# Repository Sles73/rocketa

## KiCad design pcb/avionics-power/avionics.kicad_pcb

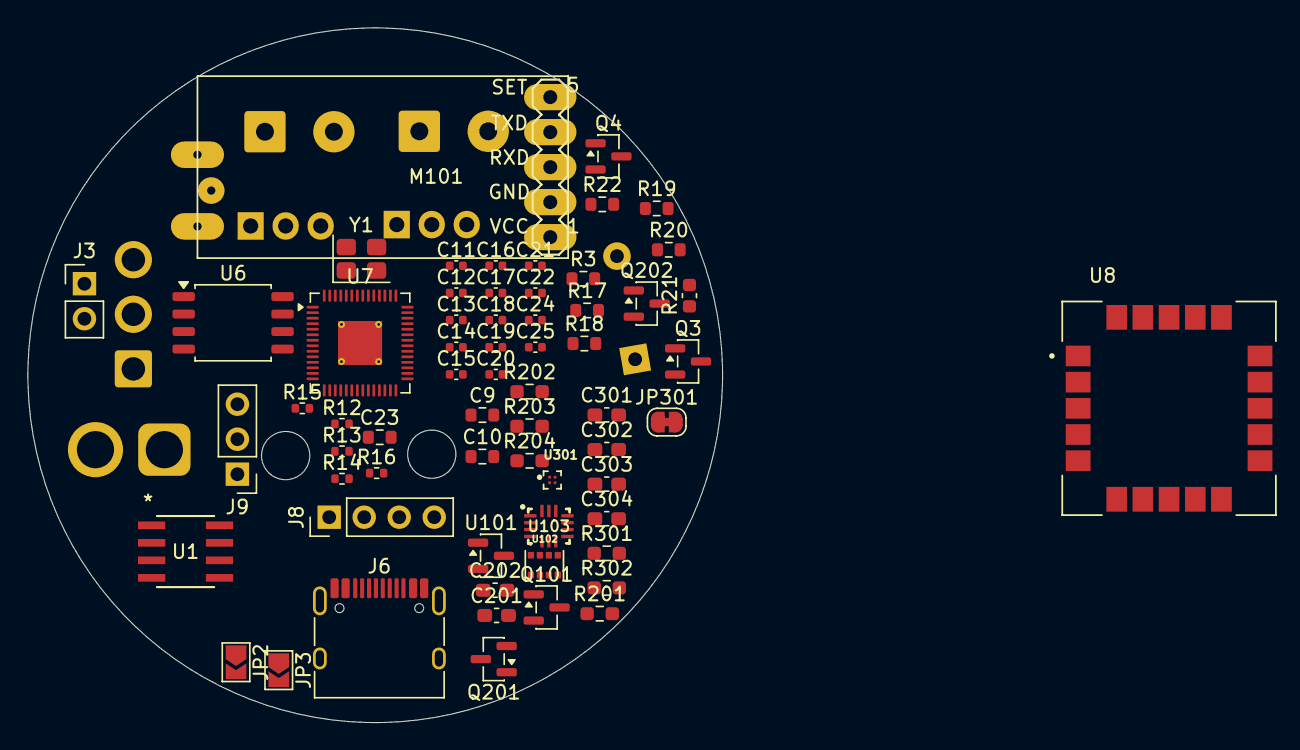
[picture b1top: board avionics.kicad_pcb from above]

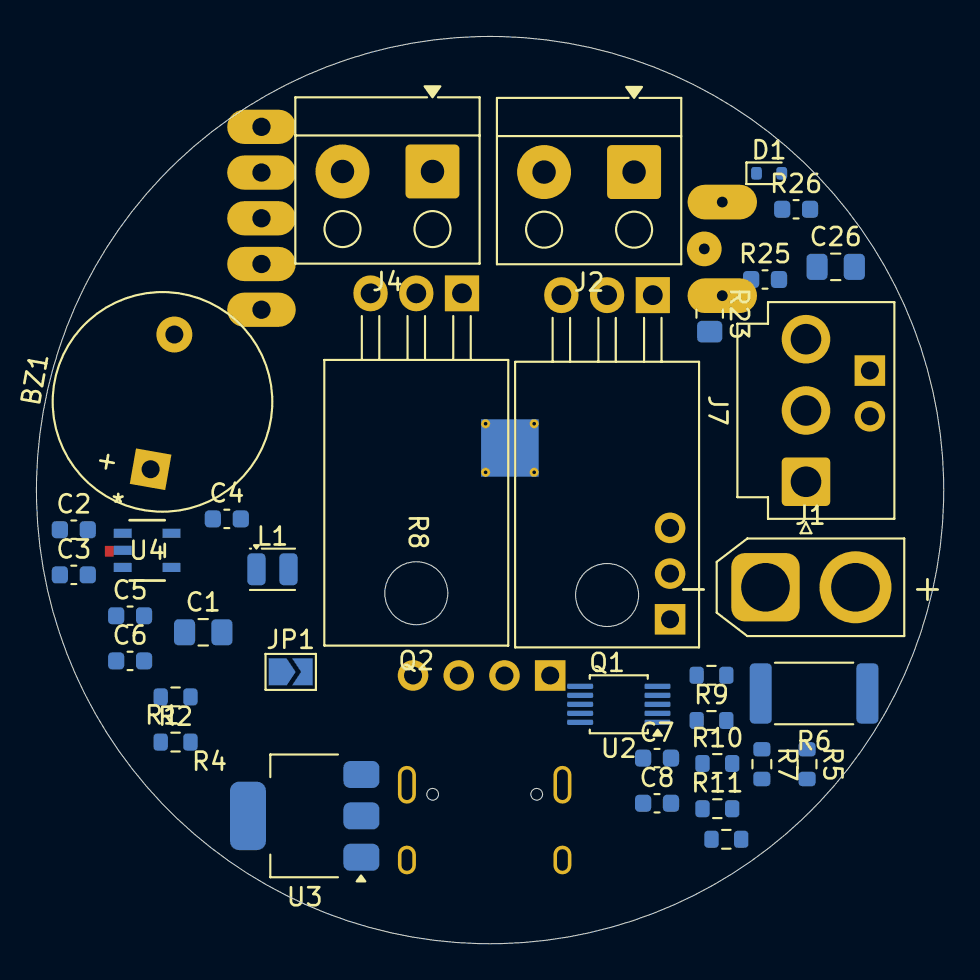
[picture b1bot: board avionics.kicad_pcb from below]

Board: 2 copper layers, 50.4 x 50.4 mm, 102 parts (35 on the bottom side), 55 nets, no tracks yet.

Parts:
BZ1: Buzzer; Buzzer_12x9.5RM7.6
C1: 22uF; C_0805_2012Metric_Pad1.18x1.45mm_HandSolder
C2: 10uF; C_0603_1608Metric
C3, C5, C6: 22uF; C_0603_1608Metric
C4: 22pF; C_0603_1608Metric
C7, C8: 100nF; C_0603_1608Metric
C9, C10, C23: 10u; R_0603_1608Metric
C11, C12, C13, C14, C15, C16, C17, C18, C19, C22: 100n; C_0402_1005Metric
C20, C21: 1u; C_0402_1005Metric
C24, C25: 15p; C_0402_1005Metric
C26: 1uF; C_0805_2012Metric_Pad1.18x1.45mm_HandSolder
C201, C202: 1uF; C_0603_1608Metric_Pad1.08x0.95mm_HandSolder
C301, C302, C303: 100nF; C_0603_1608Metric_Pad1.08x0.95mm_HandSolder
C304: 2.2uF; C_0603_1608Metric_Pad1.08x0.95mm_HandSolder
D1: ESD5Z3V3; D_SOD-523
H1, H2, H3, H4: MountingHole; MountingHole_2.7mm_M2.5
J1: Conn_batt; AMASS_XT30U-F_1x02_P5.0mm_Vertical
J2, J4: Palník_Terminal_01x02; Altech_AK100_1x02_P5.00mm
J3: Conn_01x02; PinHeader_1x02_P2.54mm_Vertical
J6: USB_C_Receptacle_USB2.0_16P; USB_C_Receptacle_HRO_TYPE-C-31-M-12
J7: RFB_switch; JST_VH_B3P-VH-B_1x03_P3.96mm_Vertical
J8: Conn_01x04_Pin; PinHeader_1x04_P2.54mm_Vertical
J9: Conn_01x03_Pin; PinHeader_1x03_P2.54mm_Vertical
JP1: SolderJumper_2_Open; SolderJumper-2_P1.3mm_Open_TrianglePad1.0x1.5mm
JP2: A1; SolderJumper-2_P1.3mm_Open_TrianglePad1.0x1.5mm
JP3: A0; SolderJumper-2_P1.3mm_Open_TrianglePad1.0x1.5mm
JP301: i2c; SolderJumper-2_P1.3mm_Bridged_RoundedPad1.0x1.5mm
L1: 2.2uH; L_Coilcraft_0805HQ_2012Metric
M101: HC-12; MA05-1
Q1, Q2: IRF9540N; TO-220-3_Horizontal_TabDown
Q3, Q4, Q202: SS8050; SOT-23
Q101, Q201: 2N7002; SOT-23
R1, R3, R7, R8, R9, R10, R11, R18, R19: 10k; R_0603_1608Metric
R2: 45k; R_0603_1608Metric
R4, R5: 10R; R_0603_1608Metric
R6: 5m; R_2512_6332Metric
R12, R13: 27; R_0402_1005Metric
R14: DNF; R_0402_1005Metric
R15, R16: 1k; R_0402_1005Metric
R17, R20, R22: 1k; R_0603_1608Metric
R21: 1k; C_0603_1608Metric
R23: 470R; R_0805_2012Metric_Pad1.20x1.40mm_HandSolder
R25: 10K; C_0603_1608Metric
R26: 18k; C_0603_1608Metric
R201, R202, R203, R204: 10k; R_0603_1608Metric_Pad0.98x0.95mm_HandSolder
R301, R302: 2.7k; R_0603_1608Metric_Pad0.98x0.95mm_HandSolder
U1: ATTINY402-SSNR; SOIC8_4P9X3P9MC_MCH
U2: INA226; TSSOP-10_3x3mm_P0.5mm
U3: AMS1117-3.3; SOT-223-3_TabPin2
U4: SY8089AAAC; SY8089AAAC_SGY
U6: W25Q128JVS; SOIC-8_5.3x5.3mm_P1.27mm
U7: RP2040; QFN-56-1EP_7x7mm_P0.4mm_EP3.2x3.2mm_ThermalVias
U8: SAM-M8Q-0-10; MODULE_SAM-M8Q-0-10
U101: ME6206A18XG; SOT-23
U102: ICP-10111; PSON65P250X200X100-8N
U103: LSM6DS3TR-C; LGA-14-2.5X3MM
U301: MMC5603NJ; XDCR_MMC5603NJ
Y1: ABM8-272-T3; Crystal_SMD_3225-4Pin_3.2x2.5mm

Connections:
+1V1: C11.1, C12.1, C20.1, U7.23 (DVDD), U7.45 (VREG_VOUT), U7.50 (DVDD)
+3V3: C4.1, C5.1, C6.1, C8.2, C10.1, C13.1, C14.1, C15.1, C16.1, C17.1, C18.1, C19.1, C21.1, C22.1, C23.1, C201.1, C301.1, C302.1, C303.1, C304.1, J8.2, J9.2, JP1.2 (B), JP2.2 (B), JP3.2 (B), JP301.1 (A), L1.2, R2.1, R9.2, R10.2, R11.2, R14.1, R202.1, R204.1, R301.1, R302.1, U1.1 (VDD), U2.6 (VS), U6.8 (VCC), U7.1 (IOVDD), U7.10 (IOVDD), U7.22 (IOVDD), U7.33 (IOVDD), U7.42 (IOVDD), U7.43 (ADC_AVDD), U7.44 (VREG_IN), U7.48 (USB_VDD), U7.49 (IOVDD), U101.3 (VI), U103.5 (VDDIO), U103.8 (VDD), U301.B1 (VDD)
+VDC: BZ1.1 (+), C1.1, C2.2, J7.1, R1.1, R5.2, R6.2, R26.1, U3.3 (VI), U4.4 (IN)
/GPS/+3V3: U8.2 (VCC_IO), U8.3 (V_BCKP), U8.17 (VCC)
/IMU/SCL: R302.2, U103.13 (SCL), U301.A2 (SCL)
/IMU/SDA: R301.2, U103.14 (SDA), U301.B2 (SDA)
/backup_mtp/palnik_backup: R20.2, U1.4 (PA1)
/barometr/SCL: Q101.3 (D), R202.2
/barometr/SDA: Q201.3 (D), R204.2
/ejection_charge_safety/Sw1: C26.1, R23.1
/ejection_charge_safety/VCC_palnik: J7.3, Q1.3 (S), Q2.3 (S), R18.2, R19.2
/mcu/QSPI_SCLK: U6.6 (CLK), U7.52 (QSPI_SCLK)
/mcu/QSPI_SD0: U6.5 (DI(IO0)), U7.53 (QSPI_SD0)
/mcu/QSPI_SD1: U6.2 (DO(IO1)), U7.55 (QSPI_SD1)
/mcu/QSPI_SD2: U6.3 (IO2), U7.54 (QSPI_SD2)
/mcu/QSPI_SD3: U6.7 (IO3), U7.51 (QSPI_SD3)
/mcu/QSPI_SS: R14.2, R15.1, U6.1 (~CS), U7.56 (QSPI_SS)
/mcu/USB_D+: J6.A6 (D+), J6.B6 (D+), R12.1
/mcu/USB_D-: J6.A7 (D-), J6.B7 (D-), R13.1
/mcu/XIN: C24.1, U7.20 (XIN), Y1.1
/mcu/XOUT: R16.1, U7.21 (XOUT)
/mcu/~USB_BOOT: J3.1, R15.2
/power_management/Alert: R11.1, U2.3 (~Alert)
/power_management/SCL: R10.1, U2.5 (SCL)
/power_management/SDA: R9.1, U2.4 (SDA)
/power_management/VCC_batt: J1.2, R4.2, R6.1, U2.8 (Vbus)
GND: C1.2, C2.1, C3.1, C5.2, C6.2, C9.2, C10.2, C11.2, C12.2, C13.2, C14.2, C15.2, C16.2, C17.2, C18.2, C19.2, C20.2, C21.2, C22.2, C23.2, C24.2, C25.2, C26.2, C201.2, C202.2, C301.2, C302.2, C303.2, C304.2, D1.2 (A), J1.1, J2.1, J3.2, J4.1, J6.A1 (GND), J6.A12 (GND), J6.B1 (GND), J6.B12 (GND), J6.SH (SHIELD), J8.1, J9.3, Q3.2 (E), Q4.2 (E), Q202.2 (E), R3.2, R7.1, R8.1, R25.2, U1.8 (GND), U2.7 (GND), U3.1 (GND), U4.2 (GND), U6.4 (GND), U7.19 (TESTEN), U7.57 (GND), U8.1 (GND), U8.4 (GND), U8.5 (GND), U8.6 (GND), U8.10 (GND), U8.11 (GND), U8.15 (GND), U8.16 (GND), U8.20 (GND), U101.1 (GND), U102.1 (GND), U102.5 (RESV5), U102.7 (GND), U103.1 (SDO/SA0), U103.2 (SDX), U103.3 (SCX), U103.6 (GND), U103.7 (GND), U301.A1 (VSA), Y1.2, Y1.4
unnamed: BZ1.2 (-), Q4.3 (C)
unnamed: C25.1, R16.2, Y1.3
unnamed: D1.1 (K), J7.2, R23.2, R25.1, R26.2
unnamed: J2.2, Q1.2 (D)
unnamed: J4.2, Q2.2 (D)
unnamed: J8.3, J9.1, R21.2, U1.6 (PA0/RESET/UPDI)
unnamed: J8.4, R21.1
unnamed: C3.2, JP1.1 (A), U3.2 (VO)
unnamed: JP2.1 (A), R7.2, U2.1 (A1)
unnamed: JP3.1 (A), R8.2, U2.2 (A0)
unnamed: JP301.2 (B), U103.12 (CS)
unnamed: M101.GND (GND1), M101.GND1
unnamed: Q1.1 (G), Q3.3 (C), R19.1
unnamed: Q2.1 (G), Q202.3 (C), R18.1
unnamed: Q3.1 (B), R20.1
unnamed: Q4.1 (B), R22.1
unnamed: C202.1, Q101.1 (G), Q201.1 (G), R201.1, R203.1, U101.2 (VO), U102.8 (VDD)
unnamed: Q101.2 (S), R201.2, U102.4 (SCL)
unnamed: Q201.2 (S), R203.2, U102.3 (SDA)
unnamed: Q202.1 (B), R17.1
unnamed: C7.1, R4.1, U2.10 (Vin+)
unnamed: C7.2, R5.1, U2.9 (Vin-)
unnamed: R1.2, U4.1 (EN)
unnamed: C4.2, R2.2, R3.1, U4.5 (FB)
unnamed: L1.1, U4.3 (LX)
unnamed: R13.2, U7.46 (USB_DM)
unnamed: R12.2, U7.47 (USB_DP)
VBUS: C9.1, J6.A4 (VBUS), J6.A9 (VBUS), J6.B4 (VBUS), J6.B9 (VBUS)

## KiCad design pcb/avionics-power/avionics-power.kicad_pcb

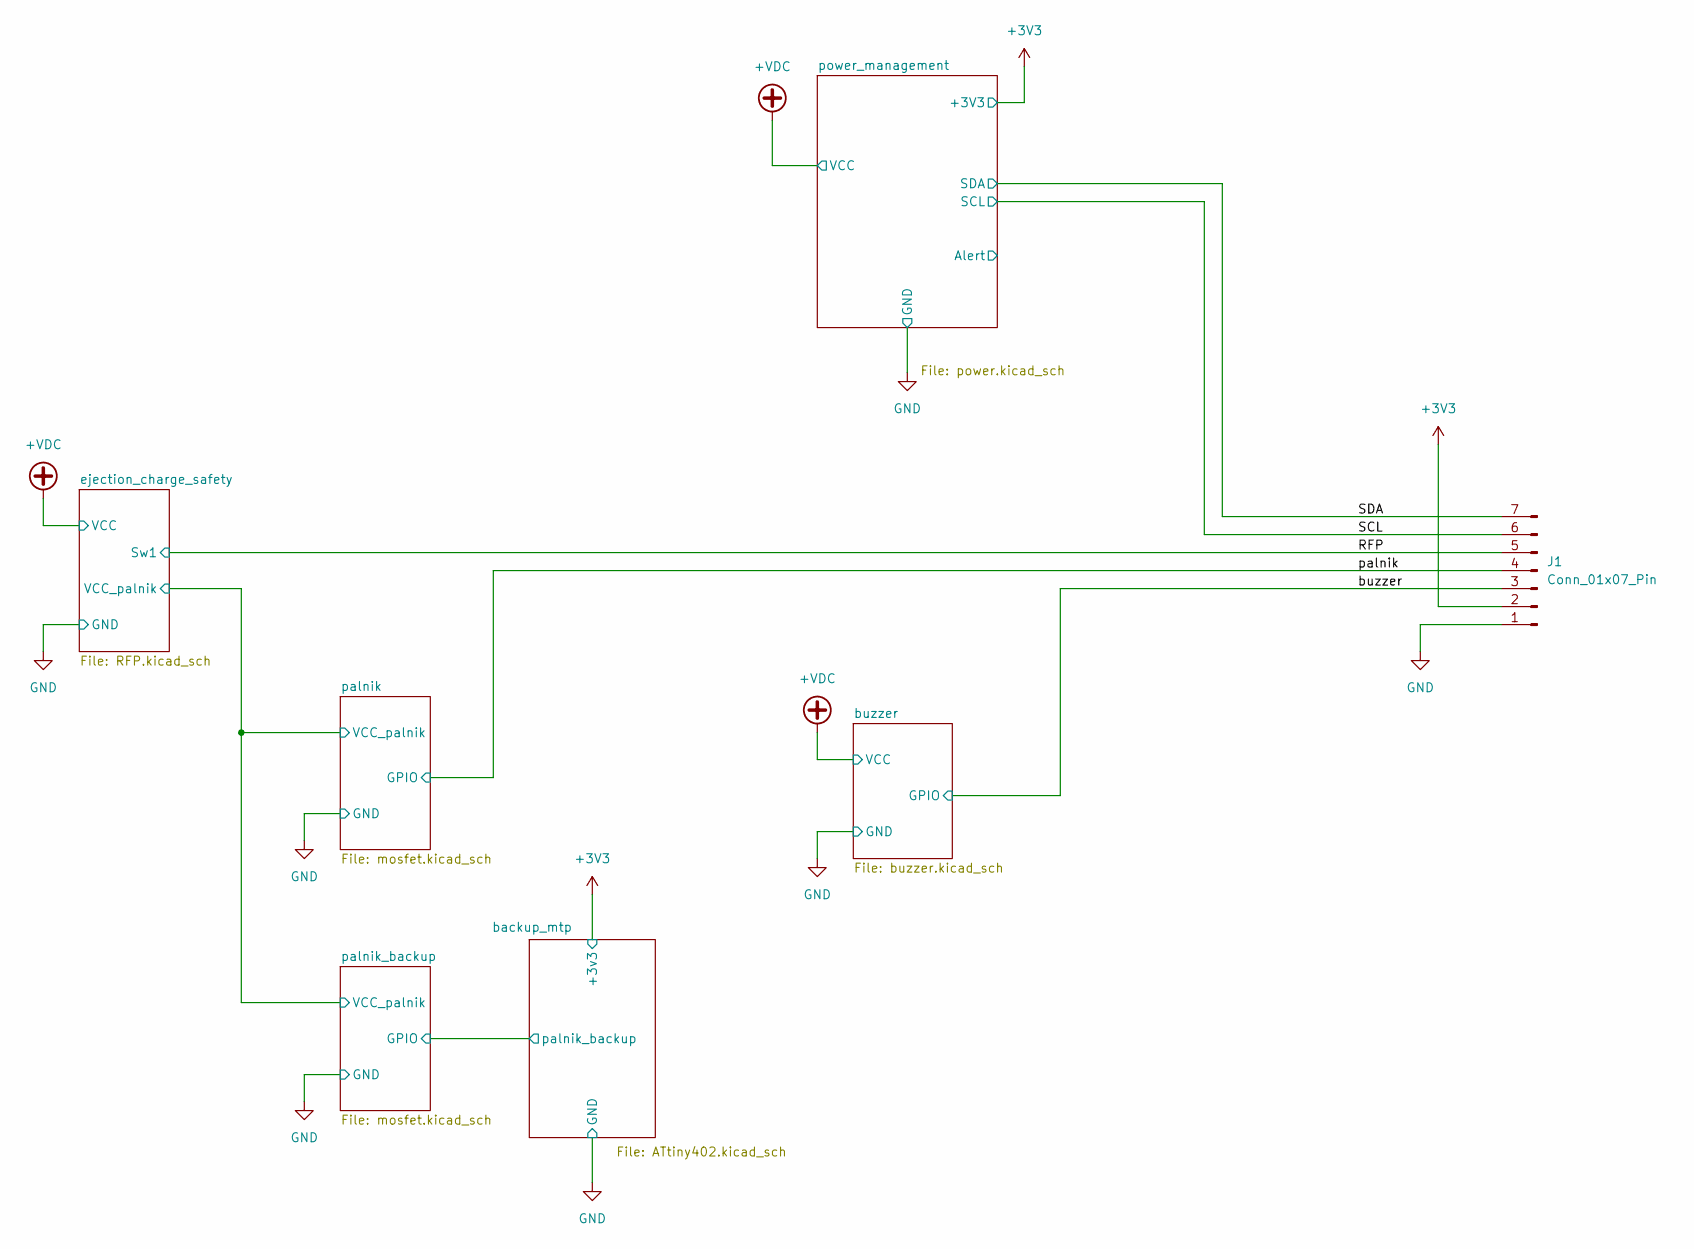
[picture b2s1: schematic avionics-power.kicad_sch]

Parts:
J1: Conn_01x07_Pin; JST_XA_S07B-XASK-1_1x07_P2.50mm_Horizontal

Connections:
+3V3: J1.2; also elsewhere on the board
/buzzer/GPIO: J1.3; also elsewhere on the board
/ejection_charge_safety/Sw1: J1.5; also elsewhere on the board
/palnik/GPIO: J1.4; also elsewhere on the board
/power_management/SCL: J1.6; also elsewhere on the board
/power_management/SDA: J1.7; also elsewhere on the board
GND: J1.1; also elsewhere on the board

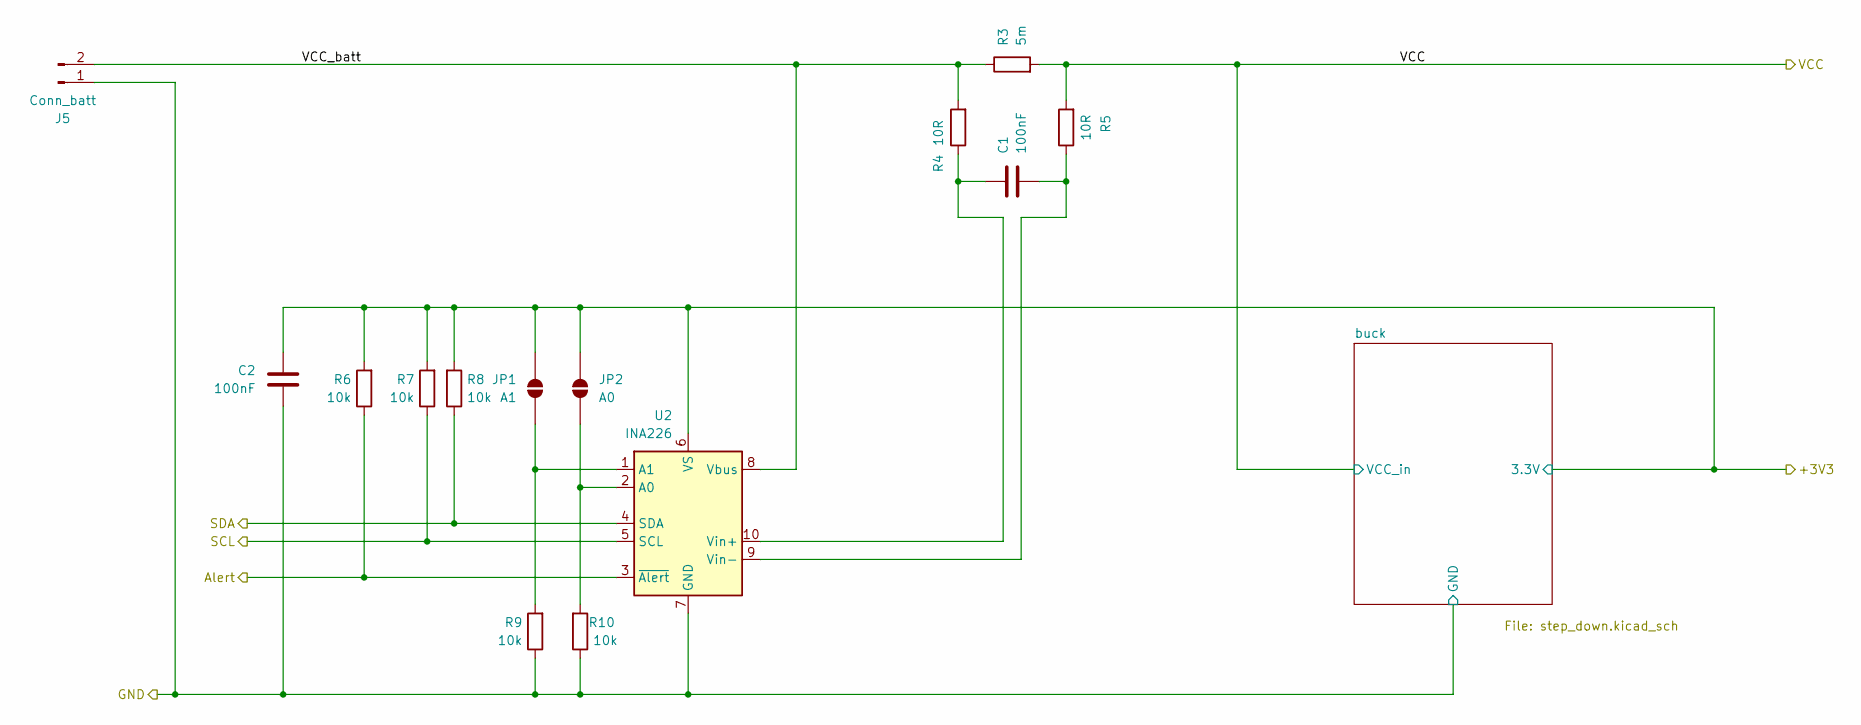
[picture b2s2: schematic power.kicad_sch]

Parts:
C1, C2: 100nF; C_0603_1608Metric
J5: Conn_batt; AMASS_XT30U-F_1x02_P5.0mm_Vertical
JP1: A1; SolderJumper-2_P1.3mm_Open_TrianglePad1.0x1.5mm
JP2: A0; SolderJumper-2_P1.3mm_Open_TrianglePad1.0x1.5mm
R3: 5m; R_2512_6332Metric
R4, R5: 10R; R_0603_1608Metric
R6, R7, R8, R9, R10: 10k; R_0603_1608Metric
U2: INA226; TSSOP-10_3x3mm_P0.5mm

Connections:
+3V3: C2.2, JP1.2 (B), JP2.2 (B), R6.2, R7.2, R8.2, U2.6 (VS); also elsewhere on the board
+VDC: R3.2, R5.2; also elsewhere on the board
/power_management/Alert: R6.1, U2.3 (~Alert)
/power_management/SCL: R7.1, U2.5 (SCL); also elsewhere on the board
/power_management/SDA: R8.1, U2.4 (SDA); also elsewhere on the board
/power_management/VCC_batt: J5.2, R3.1, R4.2, U2.8 (Vbus)
GND: C2.1, J5.1, R9.1, R10.1, U2.7 (GND); also elsewhere on the board
unnamed: JP1.1 (A), R9.2, U2.1 (A1)
unnamed: JP2.1 (A), R10.2, U2.2 (A0)
unnamed: C1.1, R4.1, U2.10 (Vin+)
unnamed: C1.2, R5.1, U2.9 (Vin-)

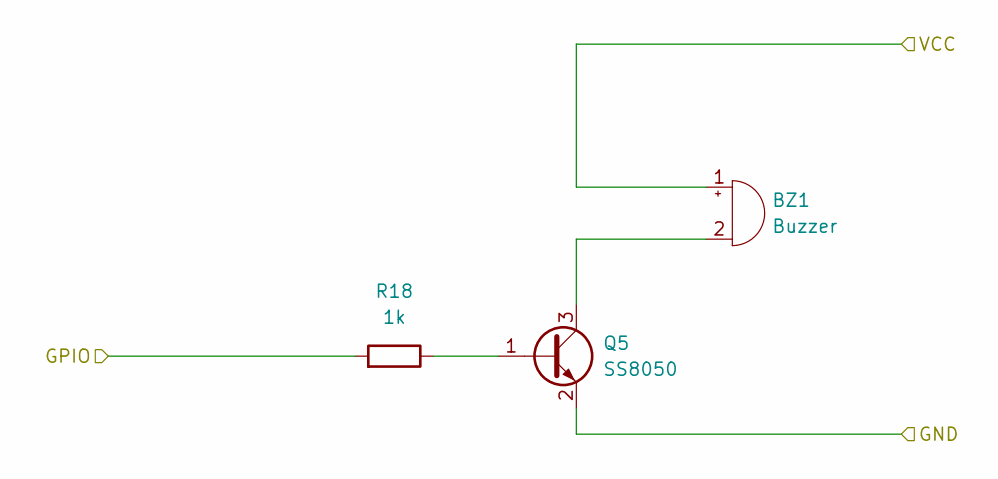
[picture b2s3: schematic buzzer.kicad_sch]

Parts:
BZ1: Buzzer; Buzzer_12x9.5RM7.6
Q5: SS8050; SOT-23
R18: 1k; R_0603_1608Metric

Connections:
+VDC: BZ1.1 (+); also elsewhere on the board
/buzzer/GPIO: R18.2; also elsewhere on the board
GND: Q5.2 (E); also elsewhere on the board
unnamed: BZ1.2 (-), Q5.3 (C)
unnamed: Q5.1 (B), R18.1

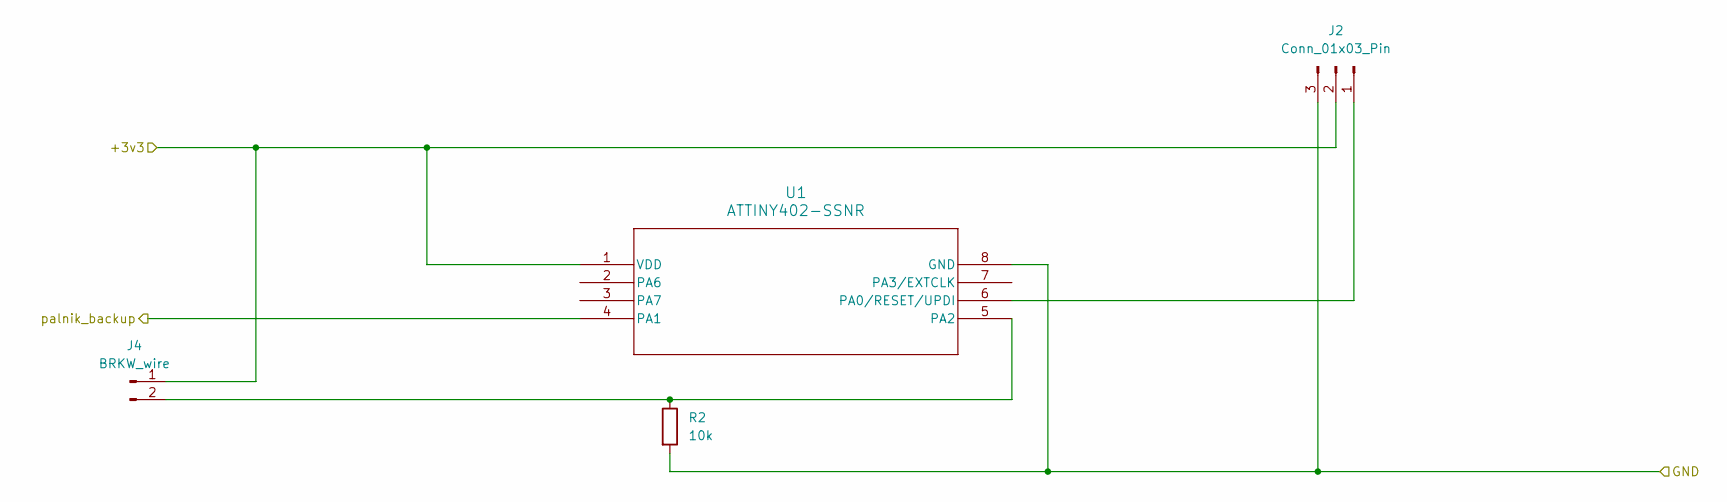
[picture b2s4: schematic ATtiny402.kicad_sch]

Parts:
J2: Conn_01x03_Pin; PinHeader_1x03_P2.54mm_Vertical
J4: BRKW_wire; JST_PH_B2B-PH-K_1x02_P2.00mm_Vertical
R2: 10k; C_0603_1608Metric
U1: ATTINY402-SSNR; SOIC8_4P9X3P9MC_MCH

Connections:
+3V3: J2.2, J4.1, U1.1 (VDD); also elsewhere on the board
/backup_mtp/palnik_backup: U1.4 (PA1); also elsewhere on the board
GND: J2.3, R2.2, U1.8 (GND); also elsewhere on the board
unnamed: J2.1, U1.6 (PA0/RESET/UPDI)
unnamed: J4.2, R2.1, U1.5 (PA2)

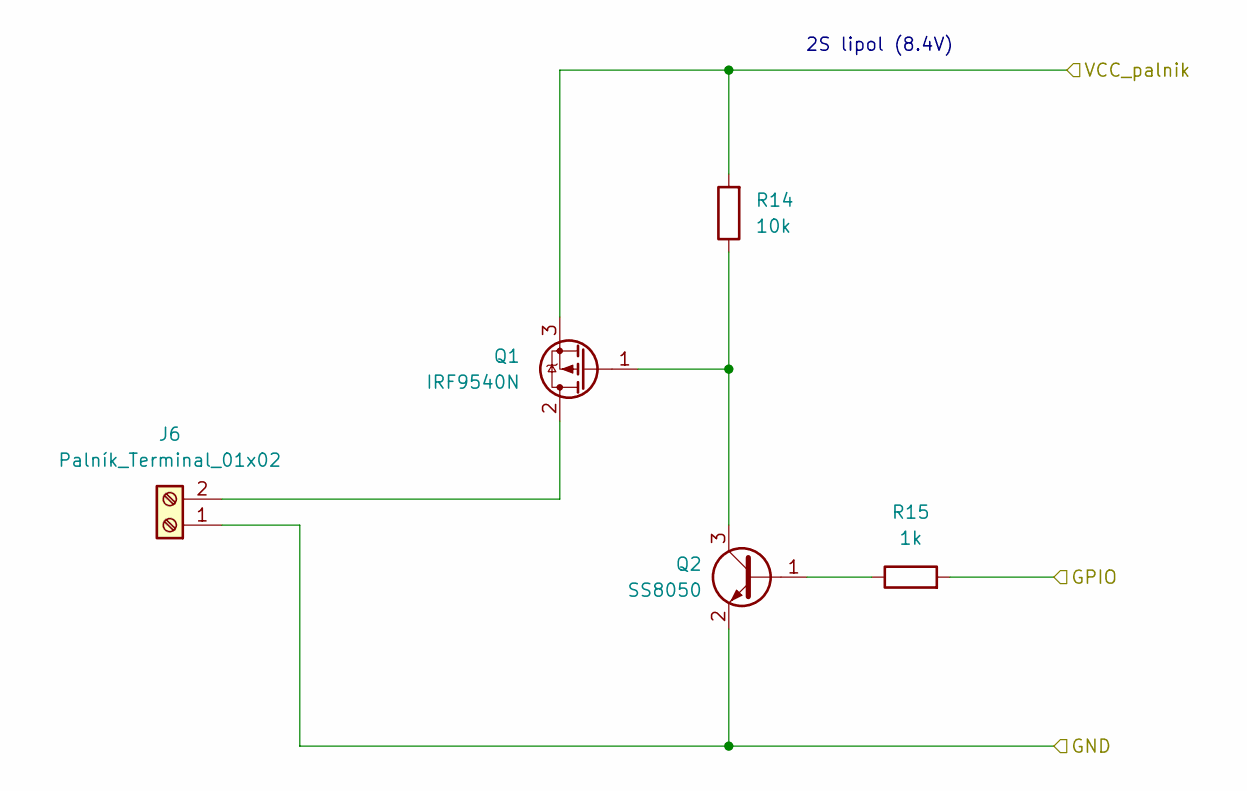
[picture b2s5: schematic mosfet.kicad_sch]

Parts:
J6: Palník_Terminal_01x02; Altech_AK100_1x02_P5.00mm
Q1: IRF9540N; TO-220-3_Horizontal_TabDown
Q2: SS8050; SOT-23
R14: 10k; R_0603_1608Metric
R15: 1k; R_0603_1608Metric

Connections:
/ejection_charge_safety/VCC_palnik: Q1.3 (S), R14.2; also elsewhere on the board
/palnik/GPIO: R15.2; also elsewhere on the board
GND: J6.1, Q2.2 (E); also elsewhere on the board
unnamed: J6.2, Q1.2 (D)
unnamed: Q1.1 (G), Q2.3 (C), R14.1
unnamed: Q2.1 (B), R15.1

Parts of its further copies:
J7: Palník_Terminal_01x02; Altech_AK100_1x02_P5.00mm
Q3: IRF9540N; TO-220-3_Horizontal_TabDown
Q4: SS8050; SOT-23
R16: 10k; R_0603_1608Metric
R17: 1k; R_0603_1608Metric

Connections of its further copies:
/backup_mtp/palnik_backup: R17.2; also elsewhere on the board
/ejection_charge_safety/VCC_palnik: Q3.3 (S), R16.2; also elsewhere on the board
GND: J7.1, Q4.2 (E); also elsewhere on the board
unnamed: J7.2, Q3.2 (D)
unnamed: Q3.1 (G), Q4.3 (C), R16.1
unnamed: Q4.1 (B), R17.1

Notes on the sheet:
2S lipol (8.4V)

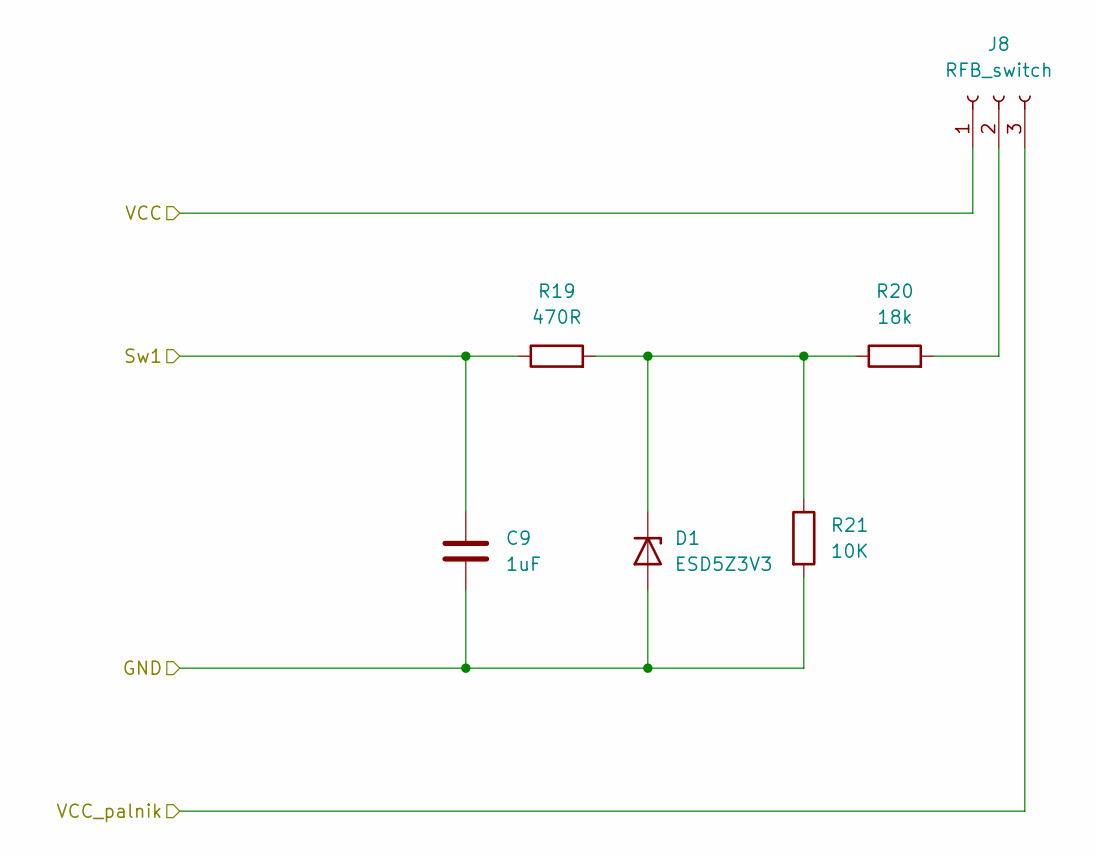
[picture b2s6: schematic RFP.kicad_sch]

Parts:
C9: 1uF; C_0805_2012Metric_Pad1.18x1.45mm_HandSolder
D1: ESD5Z3V3; D_SOD-523
J8: RFB_switch; JST_VH_B3P-VH-B_1x03_P3.96mm_Vertical
R19: 470R; R_0805_2012Metric_Pad1.20x1.40mm_HandSolder
R20: 18k; C_0603_1608Metric
R21: 10K; C_0603_1608Metric

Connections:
+VDC: J8.1; also elsewhere on the board
/ejection_charge_safety/Sw1: C9.1, R19.1; also elsewhere on the board
/ejection_charge_safety/VCC_palnik: J8.3; also elsewhere on the board
GND: C9.2, D1.2 (A), R21.2; also elsewhere on the board
unnamed: D1.1 (K), R19.2, R20.1, R21.1
unnamed: J8.2, R20.2

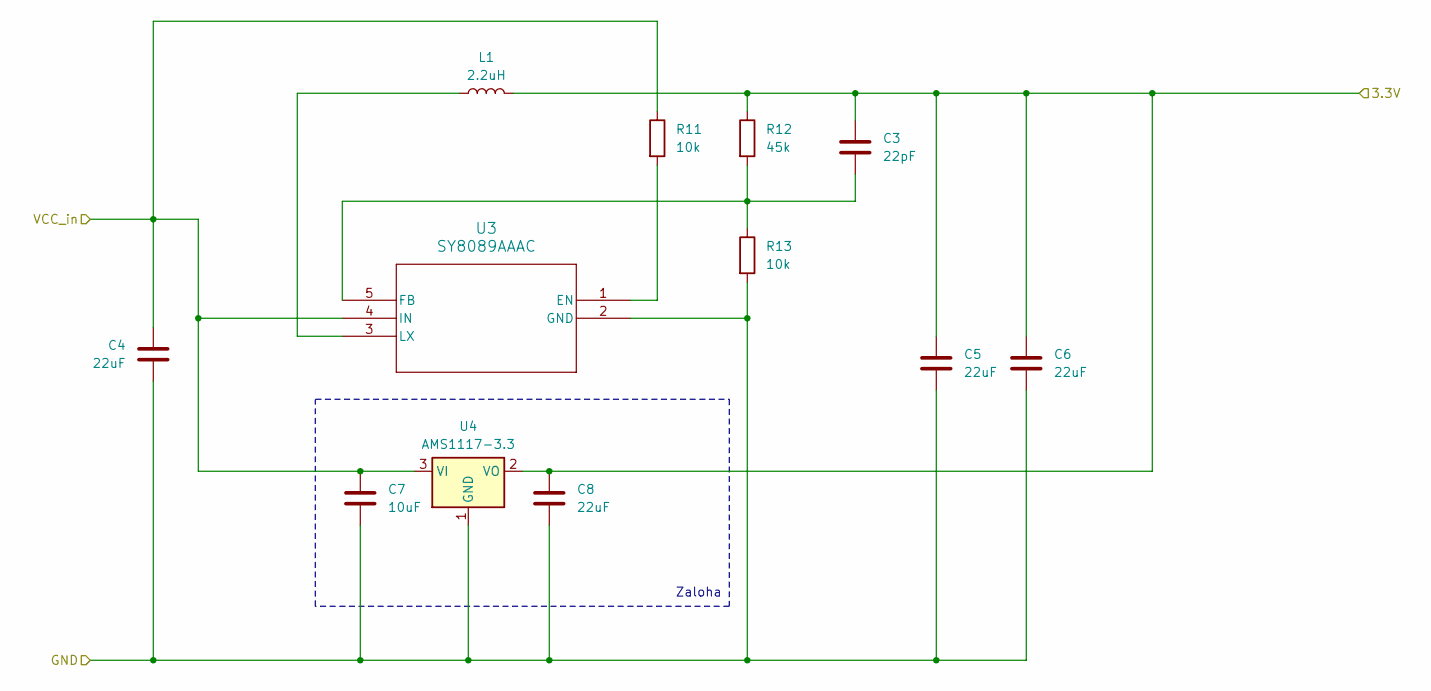
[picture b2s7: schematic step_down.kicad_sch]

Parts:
C3: 22pF; C_0603_1608Metric
C4, C5, C6, C8: 22uF; C_0603_1608Metric
C7: 10uF; C_0603_1608Metric
L1: 2.2uH; L_Coilcraft_0805HQ_2012Metric
R11, R13: 10k; R_0603_1608Metric
R12: 45k; R_0603_1608Metric
U3: SY8089AAAC; SY8089AAAC_SGY
U4: AMS1117-3.3; SOT-223-3_TabPin2

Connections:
+3V3: C3.1, C5.1, C6.1, C8.2, L1.2, R12.1, U4.2 (VO); also elsewhere on the board
+VDC: C4.1, C7.2, R11.1, U3.4 (IN), U4.3 (VI); also elsewhere on the board
GND: C4.2, C5.2, C6.2, C7.1, C8.1, R13.2, U3.2 (GND), U4.1 (GND); also elsewhere on the board
unnamed: R11.2, U3.1 (EN)
unnamed: C3.2, R12.2, R13.1, U3.5 (FB)
unnamed: L1.1, U3.3 (LX)

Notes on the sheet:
Zaloha

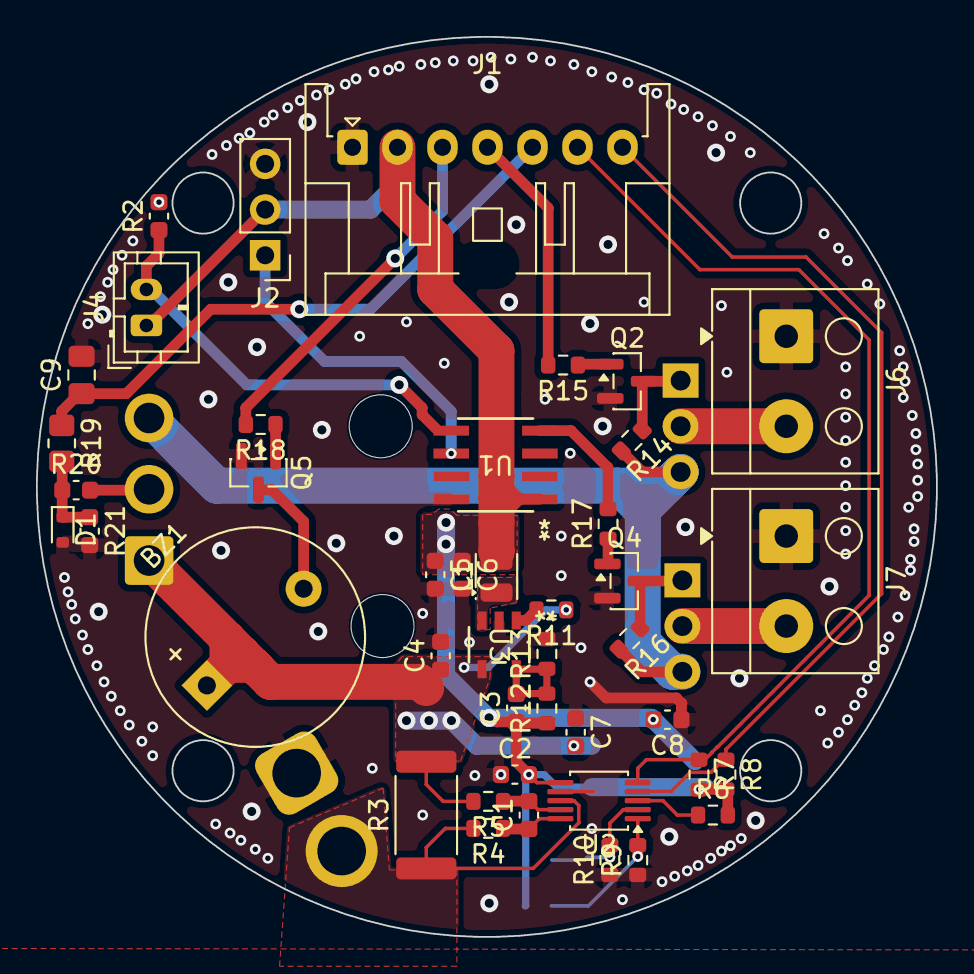
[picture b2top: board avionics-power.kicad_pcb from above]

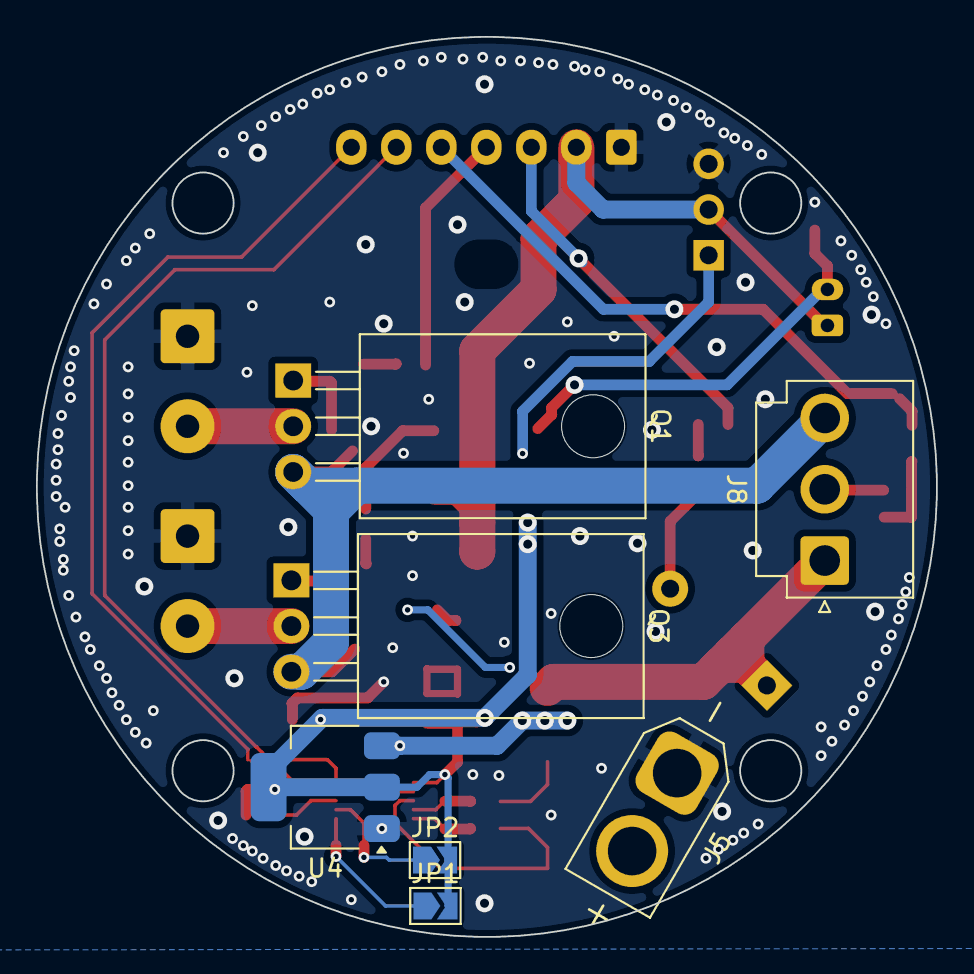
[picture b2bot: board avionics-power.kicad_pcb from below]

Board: 2 copper layers, 50.0 x 50.0 mm, 50 parts (7 on the bottom side), 31 nets.

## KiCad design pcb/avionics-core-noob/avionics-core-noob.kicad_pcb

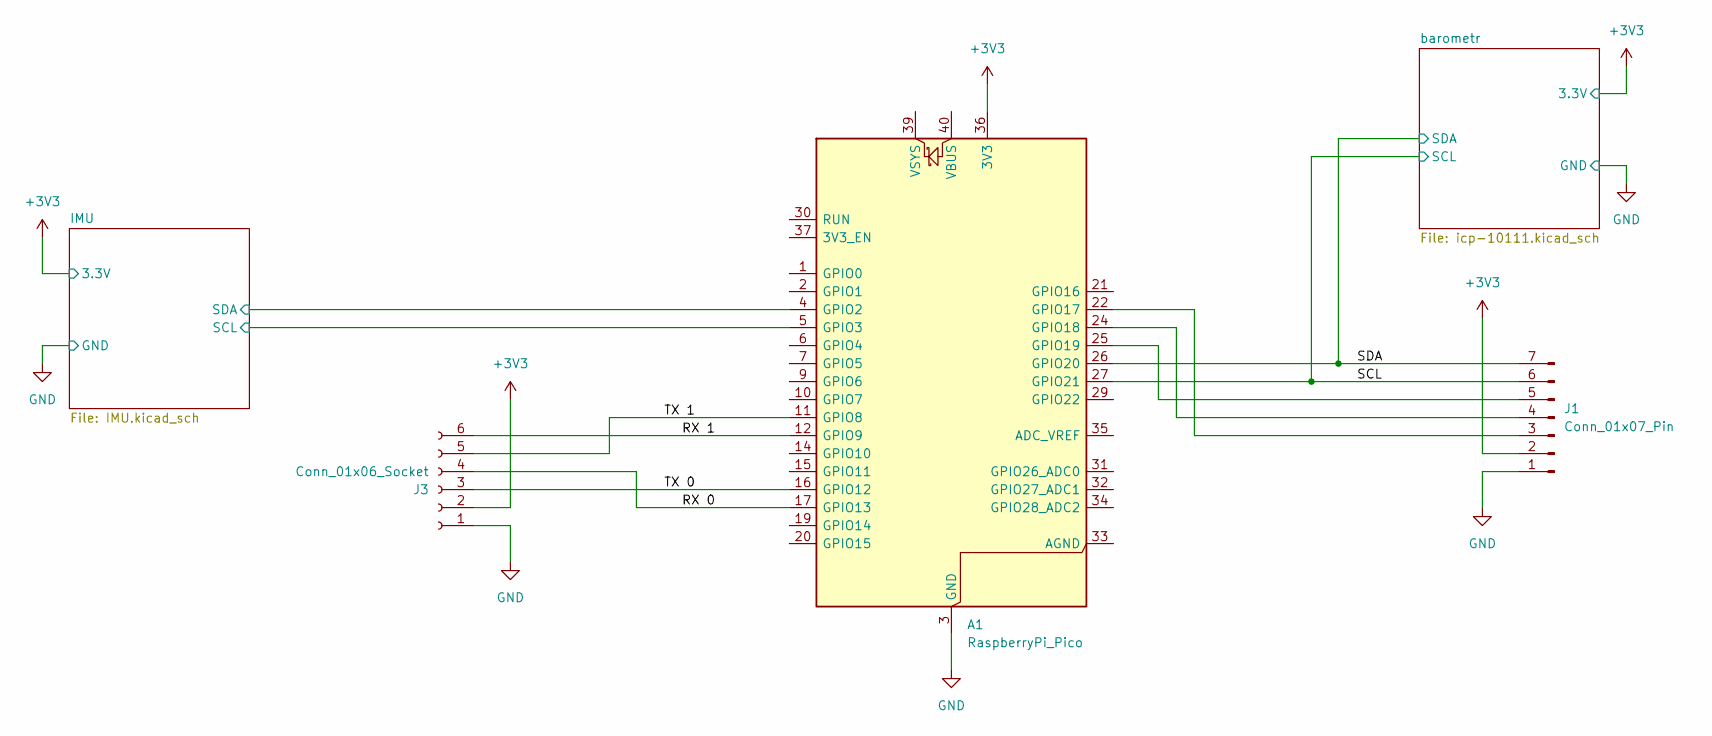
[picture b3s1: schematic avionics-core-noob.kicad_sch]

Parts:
A1: RaspberryPi_Pico; RaspberryPi_Pico_Common_Unspecified
J1: Conn_01x07_Pin; JST_XA_S07B-XASK-1_1x07_P2.50mm_Horizontal
J3: Conn_01x06_Socket; JST_XA_S06B-XASK-1_1x06_P2.50mm_Horizontal

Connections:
+3V3: A1.36 (3V3), J1.2, J3.2; also elsewhere on the board
/IMU/SCL: A1.5 (GPIO3); also elsewhere on the board
/IMU/SDA: A1.4 (GPIO2); also elsewhere on the board
/RX 0: A1.17 (GPIO13), J3.4
/RX 1: A1.12 (GPIO9), J3.6
/TX 0: A1.16 (GPIO12), J3.3
/TX 1: A1.11 (GPIO8), J3.5
/barometr/SCL: A1.27 (GPIO21), J1.6; also elsewhere on the board
/barometr/SDA: A1.26 (GPIO20), J1.7; also elsewhere on the board
GND: A1.3 (GND), A1.8 (GND), A1.13 (GND), A1.18 (GND), A1.23 (GND), A1.28 (GND), A1.38 (GND), J1.1, J3.1; also elsewhere on the board
unnamed: A1.22 (GPIO17), J1.3
unnamed: A1.24 (GPIO18), J1.4
unnamed: A1.25 (GPIO19), J1.5

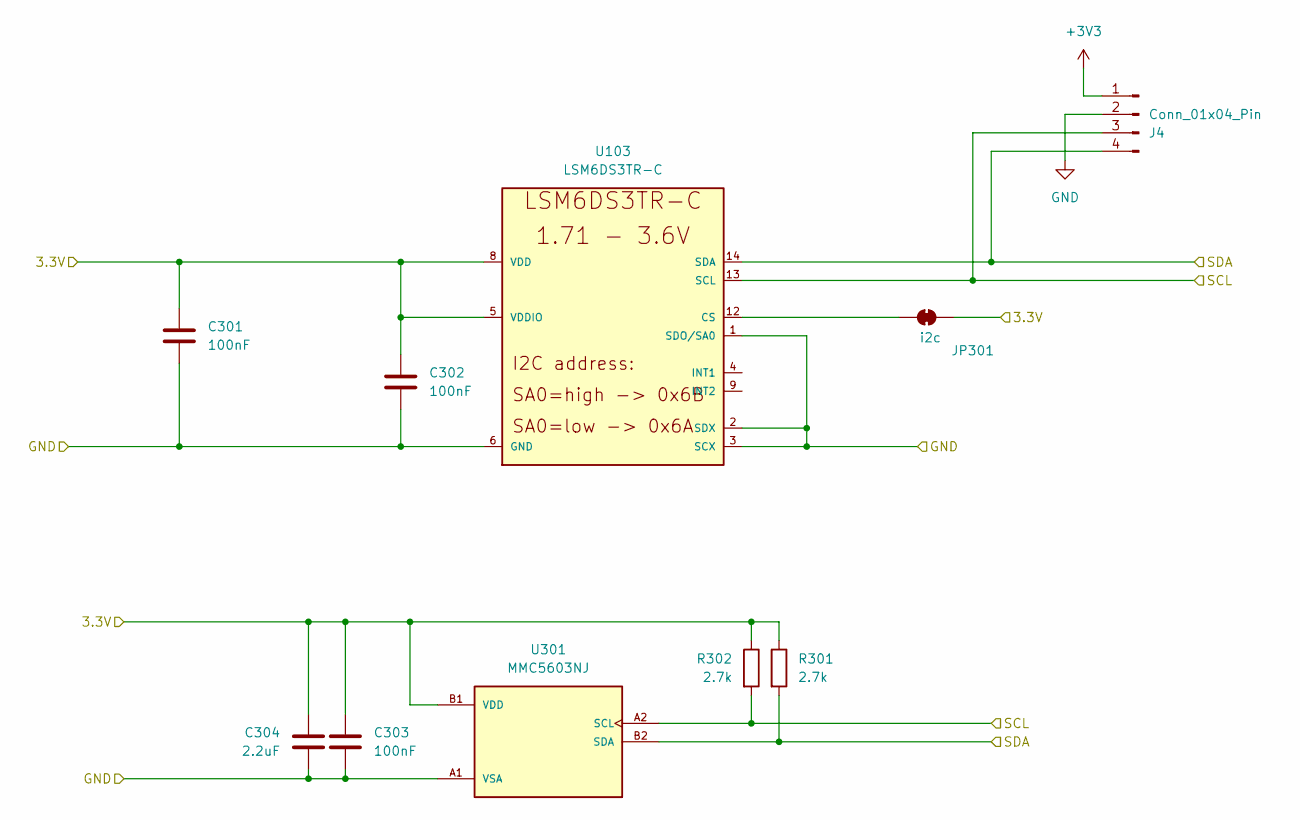
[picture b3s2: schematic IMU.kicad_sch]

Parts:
C301, C302, C303: 100nF; C_0603_1608Metric_Pad1.08x0.95mm_HandSolder
C304: 2.2uF; C_0603_1608Metric_Pad1.08x0.95mm_HandSolder
J4: Conn_01x04_Pin; PinHeader_1x04_P2.54mm_Vertical
JP301: i2c; SolderJumper-2_P1.3mm_Bridged_RoundedPad1.0x1.5mm
R301, R302: 2.7k; R_0603_1608Metric_Pad0.98x0.95mm_HandSolder
U103: LSM6DS3TR-C; LGA-14-2.5X3MM
U301: MMC5603NJ; XDCR_MMC5603NJ; PARTREV B

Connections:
+3V3: C301.1, C302.1, C303.1, C304.1, J4.1, JP301.1 (A), R301.1, R302.1, U103.5 (VDDIO), U103.8 (VDD), U301.B1 (VDD); also elsewhere on the board
/IMU/SCL: J4.3, R302.2, U103.13 (SCL), U301.A2 (SCL); also elsewhere on the board
/IMU/SDA: J4.4, R301.2, U103.14 (SDA), U301.B2 (SDA); also elsewhere on the board
GND: C301.2, C302.2, C303.2, C304.2, J4.2, U103.1 (SDO/SA0), U103.2 (SDX), U103.3 (SCX), U103.6 (GND), U103.7 (GND), U301.A1 (VSA); also elsewhere on the board
unnamed: JP301.2 (B), U103.12 (CS)

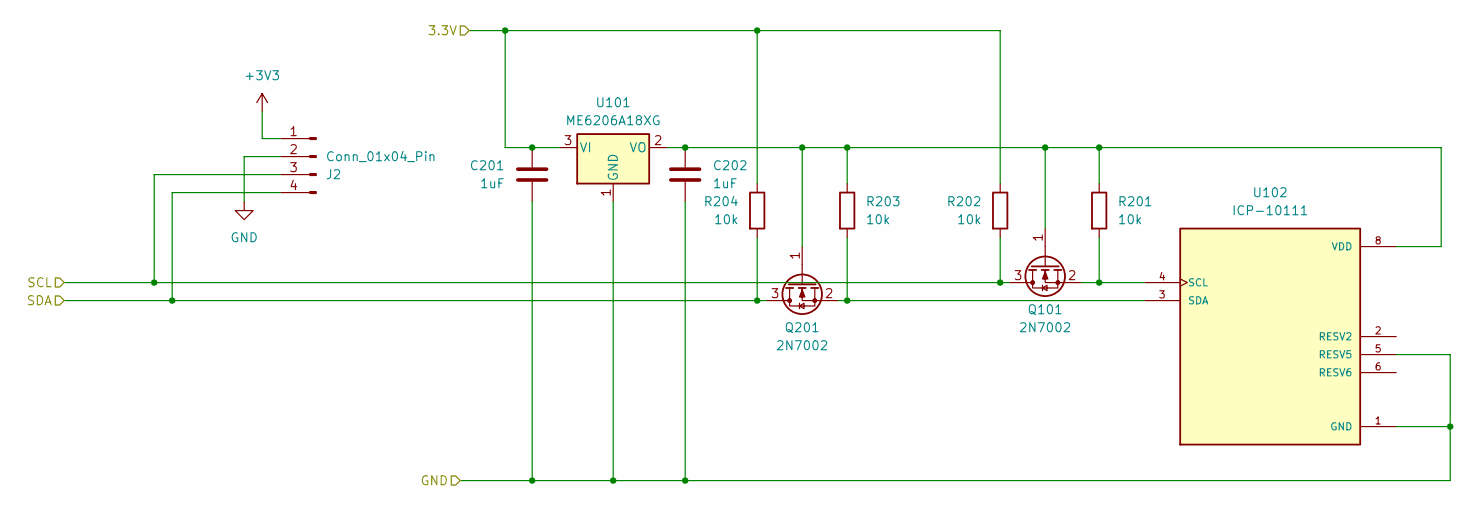
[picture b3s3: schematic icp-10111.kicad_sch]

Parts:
C201, C202: 1uF; C_0603_1608Metric_Pad1.08x0.95mm_HandSolder
J2: Conn_01x04_Pin; PinHeader_1x04_P2.54mm_Vertical
Q101, Q201: 2N7002; SOT-23
R201, R202, R203, R204: 10k; R_0603_1608Metric_Pad0.98x0.95mm_HandSolder
U101: ME6206A18XG; SOT-23
U102: ICP-10111; PSON65P250X200X100-8N; PARTREV 1.0

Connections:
+3V3: C201.1, J2.1, R202.1, R204.1, U101.3 (VI); also elsewhere on the board
/barometr/SCL: J2.3, Q101.3 (D), R202.2; also elsewhere on the board
/barometr/SDA: J2.4, Q201.3 (D), R204.2; also elsewhere on the board
GND: C201.2, C202.2, J2.2, U101.1 (GND), U102.1 (GND), U102.5 (RESV5), U102.7 (GND); also elsewhere on the board
unnamed: C202.1, Q101.1 (G), Q201.1 (G), R201.1, R203.1, U101.2 (VO), U102.8 (VDD)
unnamed: Q101.2 (S), R201.2, U102.4 (SCL)
unnamed: Q201.2 (S), R203.2, U102.3 (SDA)
